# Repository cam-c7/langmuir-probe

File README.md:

# Welcome to langmuir-probe!
The home base for a variety of file types including PCB layouts, LabView programs, and python scripts for [Autumn](https://github.com/autumnzaretsky) and [Cameron](https://github.com/cam-c7)'s ongoing langmuir probe project.

### Read about the project here:
[AME and ASTE Students Awarded at the 2024 AIAA Conference](https://viterbischool.usc.edu/news/2024/04/ame-students-awarded-at-the-2024-aiaa-conference/)

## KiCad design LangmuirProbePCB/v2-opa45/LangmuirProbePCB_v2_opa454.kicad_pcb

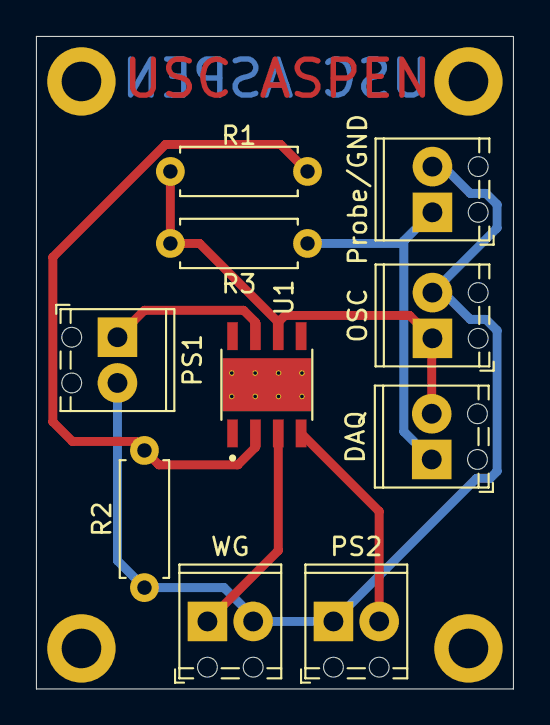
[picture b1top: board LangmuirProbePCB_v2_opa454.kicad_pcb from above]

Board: 2 copper layers, 26.5 x 36.2 mm, 10 parts (0 on the bottom side), 7 nets.

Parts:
DAQ: Screw_Terminal_01x02; TerminalBlock_Phoenix_MPT-0,5-2-2.54_1x02_P2.54mm_Horizontal
OSC: Screw_Terminal_01x02; TerminalBlock_Phoenix_MPT-0,5-2-2.54_1x02_P2.54mm_Horizontal
PS1, PS2: Screw_Terminal_01x02; TerminalBlock_Phoenix_MPT-0,5-2-2.54_1x02_P2.54mm_Horizontal
Probe/GND: Screw_Terminal_01x02; TerminalBlock_Phoenix_MPT-0,5-2-2.54_1x02_P2.54mm_Horizontal
R1: 5.1 ohms; R_Axial_DIN0207_L6.3mm_D2.5mm_P7.62mm_Horizontal
R2: 2 ohms; R_Axial_DIN0207_L6.3mm_D2.5mm_P7.62mm_Horizontal
R3: x ohms; R_Axial_DIN0207_L6.3mm_D2.5mm_P7.62mm_Horizontal
U1: OPA454; VREG_LM5017MR_NOPB
WG: Screw_Terminal_01x02; TerminalBlock_Phoenix_MPT-0,5-2-2.54_1x02_P2.54mm_Horizontal

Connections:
unnamed: DAQ.1, Probe/GND.1, R3.2
unnamed: DAQ.2, OSC.1, R1.2, R3.1, U1.6
unnamed: OSC.2, PS1.2, PS2.1, Probe/GND.2, R2.1, WG.2
unnamed: PS1.1, U1.7 (V+)
unnamed: PS2.2, U1.4 (V-)
unnamed: U1.3 (+), WG.1
unnamed: R1.1, R2.2, U1.2 (-)

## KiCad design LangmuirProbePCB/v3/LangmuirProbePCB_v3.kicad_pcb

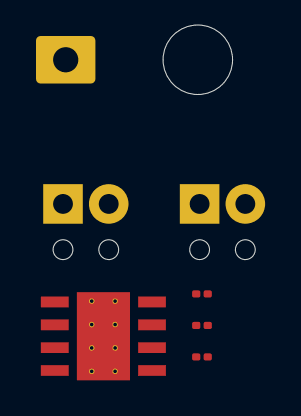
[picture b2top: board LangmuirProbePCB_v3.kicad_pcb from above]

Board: 2 copper layers, 7 parts (0 on the bottom side), 6 nets, no tracks yet.

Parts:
C1, C2, C3: 0.1 muF; C_0201_0603Metric
J1: Screw_Terminal_01x02; TerminalBlock_Phoenix_MPT-0,5-2-2.54_1x02_P2.54mm_Horizontal
J2: WFG; TerminalBlock_Phoenix_MPT-0,5-2-2.54_1x02_P2.54mm_Horizontal
J3: Vout; TE_MATE-N-LOK_1-794374-x_1x01_P4.14mm_Horizontal
U1: OPA454AIDDA; VREG_LM5017MR_NOPB

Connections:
unnamed: C3.2, J1.1, U1.7 (V+)
unnamed: C1.2, C2.2, J1.2, U1.1 (E/D_COM), U1.4 (V-), U1.9 (POWER_PAD)
unnamed: J2.1, U1.3 (+IN)
unnamed: C2.1, C3.1, J2.2
unnamed: J3.1, U1.6 (OUT)
unnamed: C1.1, U1.8 (E/D)

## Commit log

2024-02-15 Added LabView Program
2024-02-15 Added Arduino File
2024-02-20 Initial Commit
    Doesn't work yet
2024-05-13 added KiCad files for PCB
2024-05-14 added v3 with OPA454
2024-05-16 not finished but what I have so far of opa454 stuff
2024-05-20 added mounting holes
2024-05-20 started NX file for case and organized v2_opa454 folder
2024-05-21 first iteration of pcb box
2024-05-30 small pcb box changes
2024-09-04 board final
2024-09-04 usc aspen
2024-09-04 removing unnecessary numbers to make me happy
